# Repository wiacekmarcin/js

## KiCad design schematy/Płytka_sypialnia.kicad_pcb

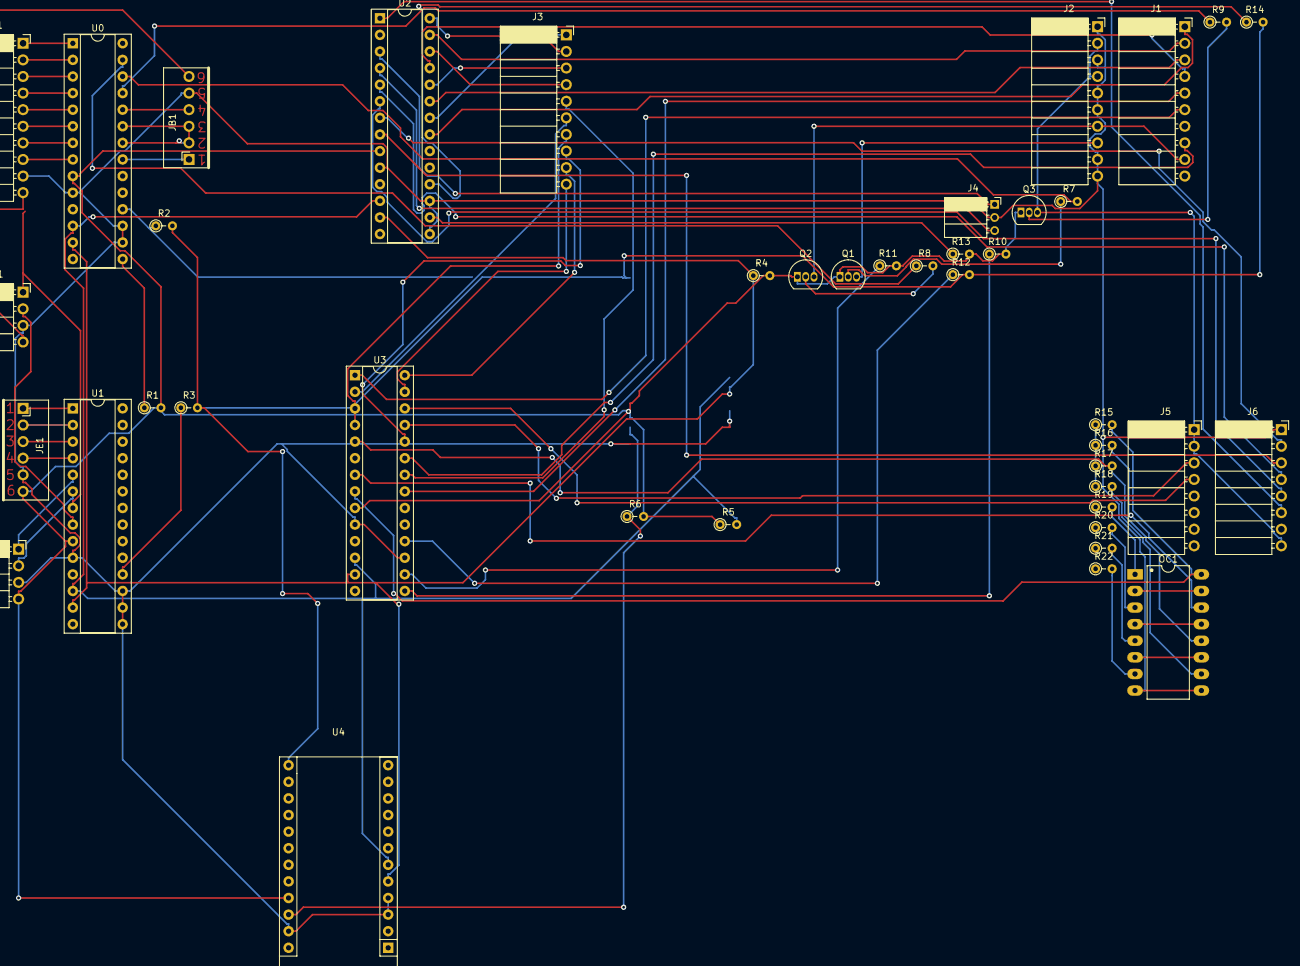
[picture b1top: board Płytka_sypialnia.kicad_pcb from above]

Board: 2 copper layers, 42 parts (0 on the bottom side), 80 nets.

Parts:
J1: F214; PinSocket_1x10_P2.54mm_Horizontal
J2: G215; PinSocket_1x10_P2.54mm_Horizontal
J3: H216; PinSocket_1x10_P2.54mm_Horizontal
J4: I217; PinSocket_1x03_P2.00mm_Horizontal
J5: K59; PinSocket_1x08_P2.54mm_Horizontal
J6: J58; PinSocket_1x08_P2.54mm_Horizontal
JA1: A209; PinSocket_1x10_P2.54mm_Horizontal
JB1: B213; PinSocket_Yellow_1x06_P2.54mm_Horizontal
JC1: C211; PinSocket_1x04_P2.54mm_Horizontal
JD1: D212; PinSocket_1x04_P2.54mm_Horizontal
JE1: E210; PinSocket_Yellow_1x06_P2.54mm_Horizontal
OC1: ILQ621-X006; DIP-16_W10.16mm_LongPads
Q1, Q2, Q3: BC337; TO-92_Inline
R1, R2, R3, R6, R10, R11, R12, R13, R14: 10K; R_Axial_DIN0204_L3.6mm_D1.6mm_P2.54mm_Vertical
R4, R5: 4.7K; R_Axial_DIN0204_L3.6mm_D1.6mm_P2.54mm_Vertical
R7, R8, R9: 100; R_Axial_DIN0204_L3.6mm_D1.6mm_P2.54mm_Vertical
R15, R16, R17, R18: 4.7k; R_Axial_DIN0204_L3.6mm_D1.6mm_P2.54mm_Vertical
R19, R20, R21, R22: 470; R_Axial_DIN0204_L3.6mm_D1.6mm_P2.54mm_Vertical
U0, U1, U2, U3: MCP23017_SP; DIP-28_W7.62mm_Socket
U4: Sparkfun_Pro_Micro

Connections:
2TARYFA: OC1.10, R18.2
5V_CONST: JD1.4, JE1.6, Q1.1 (C), Q2.1 (C), Q3.1 (C), R1.2, R4.2, R5.1, R6.2, R10.2, R11.2, R13.2, U0.9 (VDD), U1.9 (VDD), U2.9 (VDD), U3.9 (VDD), U4.21 (VCC)
5V_OFF: JA1.10, JB1.6, JC1.4
/MCP0_B0: JE1.1, U1.1 (GPB0)
/MCP0_B1: JE1.2, U1.2 (GPB1)
/MCP0_B2: JE1.3, U1.3 (GPB2)
/MCP0_B3: JE1.4, U1.4 (GPB3)
/MCP0_B4: JD1.1, U1.5 (GPB4)
/MCP0_B5: JD1.2, U1.6 (GPB5)
/MCP0_B6: JC1.1, U1.7 (GPB6)
/MCP0_B7: JC1.2, U1.8 (GPB7)
/MCP1_A0: JB1.1, U0.21 (GPA0)
/MCP1_A1: JB1.2, U0.22 (GPA1)
/MCP1_A2: JB1.3, U0.23 (GPA2)
/MCP1_A3: JB1.4, U0.24 (GPA3)
/MCP1_A4: R9.1, U0.25 (GPA4)
/MCP1_A5: R7.2, U0.26 (GPA5)
/MCP1_A6: R8.1, U0.27 (GPA6)
/MCP1_B0: JA1.1, U0.1 (GPB0)
/MCP1_B1: JA1.2, U0.2 (GPB1)
/MCP1_B2: JA1.3, U0.3 (GPB2)
/MCP1_B3: JA1.4, U0.4 (GPB3)
/MCP1_B4: JA1.5, U0.5 (GPB4)
/MCP1_B5: JA1.6, U0.6 (GPB5)
/MCP1_B6: JA1.7, U0.7 (GPB6)
/MCP1_B7: JA1.8, U0.8 (GPB7)
/PODSW_HOL: J1.9, J2.7, Q2.3 (E)
/PODSW_MIX: J2.8, Q1.3 (E)
/PODSW_SAL: J2.2, J2.4, J5.1, J5.2, J6.8, Q3.3 (E)
GND: J2.1, J2.3, J2.5, J2.6, J2.9, J2.10, J4.2, J6.1, JA1.9, JB1.5, JC1.3, JD1.3, JE1.5, OC1.2, OC1.4, OC1.6, OC1.8, OC1.9, OC1.11, OC1.13, OC1.15, U0.10 (VSS), U0.16 (A1), U0.17 (A2), U1.10 (VSS), U1.15 (A0), U1.16 (A1), U1.17 (A2), U2.10 (VSS), U2.15 (A0), U2.17 (A2), U3.10 (VSS), U3.17 (A2), U4.3 (GND), U4.4 (GND), U4.23 (GND)
I2C_SCK: R5.2, U0.12 (SCK), U1.12 (SCK), U2.12 (SCK), U3.12 (SCK), U4.6 (~D3)
I2C_SDA: R4.1, U0.13 (SDA), U1.13 (SDA), U2.13 (SDA), U3.13 (SDA), U4.5 (D2)
KL_HOL_DRZWI: J3.10, U3.27 (GPA6)
KL_HOL_L_L: J1.8, U3.23 (GPA2)
KL_HOL_L_P: J3.8, U3.24 (GPA3)
KL_HOL_P_1: J3.9, U3.28 (GPA7)
KL_HOL_SL_P: J3.7, U3.3 (GPB2), U3.4 (GPB3)
KL_HOL_SP_L: J1.6, U3.1 (GPB0)
KL_HOL_SP_P: J3.6, U3.2 (GPB1)
KL_HOL_W_L: J5.3, U3.25 (GPA4)
KL_HOL_W_P: J5.4, U3.26 (GPA5)
KL_SAL_JL_L: J6.2, U2.7 (GPB6)
KL_SAL_JL_P: J6.3, U2.8 (GPB7)
KL_SAL_JP_L: J6.4, U2.5 (GPB4)
KL_SAL_JP_P: J6.5, U2.6 (GPB5)
KL_SAL_KL_L: J4.1, U2.3 (GPB2)
KL_SAL_KL_P: J4.3, U2.4 (GPB3)
KL_SAL_KP_L: J6.6, U2.1 (GPB0)
KL_SAL_KP_P: J6.7, U2.2 (GPB1)
KL_SAL_L: J1.2, U2.27 (GPA6)
KL_SAL_L_L: J1.5, U3.21 (GPA0)
KL_SAL_L_P: J3.5, U3.22 (GPA1)
KL_SAL_P: J3.2, U2.28 (GPA7)
KL_SAL_SL_L: J1.3, U2.23 (GPA2)
KL_SAL_SL_P: J3.3, U2.24 (GPA3)
KL_SAL_SP_L: J1.4, U2.25 (GPA4)
KL_SAL_SP_P: J3.4, U2.26 (GPA5)
KL_SYP_L: J1.1, U2.21 (GPA0)
KL_SYP_P: J3.1, U2.22 (GPA1)
NOC: OC1.14, R16.2, U3.7 (GPB6)
unnamed: OC1.1, R19.2
unnamed: OC1.3, R20.2
unnamed: OC1.5, R21.2
unnamed: OC1.7, R22.2
unnamed: Q1.2 (B), R7.1
unnamed: Q2.2 (B), R8.2
unnamed: Q3.2 (B), R9.2
unnamed: R15.1, R16.1, R17.1, R18.1
unnamed: R1.1, U0.15 (A0)
unnamed: R2.1, U0.18 (~RESET)
unnamed: R3.1, U1.18 (~RESET)
unnamed: R13.1, U2.16 (A1)
unnamed: R14.1, U2.18 (~RESET)
unnamed: R10.1, U3.15 (A0)
unnamed: R11.1, U3.16 (A1)
unnamed: R12.1, U3.18 (~RESET)
unnamed: R6.1, U4.22 (RST)
RESET_MCP: R2.2, R3.2, R12.2, R14.2, U4.13 (~D10/A10)
WIECZOR: OC1.16, R15.2, U3.8 (GPB7)
ZAS.AWAR: OC1.12, R17.2, U3.5 (GPB4)

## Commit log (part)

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2024-01-02 Kolejna wersja
2024-01-03 Porzadki z mysensor - kompilacja
2024-02-07 Przeniesiono bazę na rapsberry plus dodanie 204-207 przewody
2025-01-23 Wersja przed scalaniem
2025-01-24 Jakies zmiany
2025-01-24 Pierwsza wersja
2025-01-24 Drobne porawki
2025-01-24 szczegoly przeniesione do przewody.details
2025-01-24 Dodano elementy płytkowe i piny do elementów płytkowych
2025-01-24 Zmiana tabeli miejsca
2025-01-24 Dodano urżądzenia końcowe
2025-01-24 Uporządkowano listę miejsc
2025-01-24 Zmiana koncepcji listy przewodow
2025-01-24 Jakieś zmiany
2025-01-24 Poprawki dotyczace przewodu_list
2025-01-24 Drobne poprawki
2025-01-24 Działająca wersja przewodów
2025-01-24 Przed wprowaddzeniem ng-include
2025-01-24 Dodano obsługę połączeń
2025-01-24 Dodano pliki od dodawania polaczenia, zlacza, zyly
2025-01-24 Dodawanie nazwanych łącz cz I (nieskoczone)
2025-01-24 Połączenie na płytce widok
2025-01-24 Dodawanie zakończeń po stronie płutki zakończone
2025-01-24 Dodawanie żył i połączeń
2025-01-24 Rozpoczęcie zmian z dodawaniem połączeń na płytkach
2025-01-24 dodano zlacze_add
2025-01-24 Uzupelniono liste miejsc
2025-01-24 Dodano obsluge edycji i dodawania nowego złącza
2025-01-24 Dodano "dodawanie zakonczenia"
2025-01-24 Ostatnie zmiany przed rewolucja (zlacze_id i miejsce_id w jednje tabeli jako podwójny index zamiast jednego)
2025-01-24 Drobne poprawki z wyświetlaniem
2025-01-24 Zrobione kolory miejsca
2025-01-24 Dodawanie.zakonczenia part 2/3
2025-01-24 Przewody wystwielanie edycja dodawanie
2025-01-24 Dodano elementy plytki
2025-01-24 Spacje
2025-01-24 Zmiana z tinyint na smallint dla elementy_plytkowe
2025-01-24 Drobne poprawki w wyglądzie przewodów
2025-01-24 Poprawki w bazie
2025-01-24 Zmiany w przewodach
2025-01-24 Kolejne praca nad przewodami
2025-01-24 Uporządkowano przewody - przed zmiany w tablicy polaczenia
2025-01-24 Poprawiono elementy płytkowe
2025-01-24 Dodano dodawanie żył
2025-01-24 Dodano zakonczenia
2025-01-24 Wersja z dodawanie pinow do zakonczenia
2025-01-24 Troche danych
2025-01-24 Sporo nowych danych
2025-01-24 Dodano urządzenia kablowe
2025-01-24 Przed wkopiowaniem nowych polaczen
2025-01-24 Wstawianie pinow do urzadzen kablowych - nie testowane
2025-01-24 Dodano definicje plytki A
2025-01-24 Dodano wstawianie żył
2025-01-24 Rozpoczeęcie prac nad dodawanie pinów do złacza
2025-01-24 Dodano wejsje min plikow angular i angular-route
2025-01-24 Porządki w rozdzielni
2025-01-24 Dodano polaczneia plytki B w przedpokoju
2025-01-24 Dodano przeplywomierz dla lazienki
2025-01-24 Kolejne żyły
2025-01-24 Doanie przewodu 29 ze złaczami i wtyczkami
2025-01-24 Zmiany związane dodaniem złacza-właczki.
2025-01-24 Dalsze prace nad przepływomierzami
2025-01-24 zmiany w sql
2025-01-24 Dodawanie w bazie danych
2025-01-24 Poprawki i nowae dane
2025-01-24 Przeniesiono do katalogu przewody
2025-01-24 Wersja 25-01-24
2025-01-24 Dodanie PrzeplywomierzaDomowego
2025-01-24 Zmiana katalogu
2025-01-24 Initial version
2025-01-24 Pierwsze testy nie udane
2025-01-24 Porzadki z katalogiem
2025-01-24 [WC] Poprawka z temperaturą
2025-01-24 Dodanie settings.json
2025-01-24 WC przesunięcie do katalogu
2025-01-24 jakas wersja
2025-01-24 Poprawki w extensions.json
2025-01-24 initial
2025-01-24 Ddaonie funkcji print dla wyjsc
2025-01-24 Porządki
2025-01-24 Pierwsza kompilujaca sie wersja
2025-01-24 Uporzadkowano lustro
2025-01-24 Wersja do testowania
2025-01-24 Testy i testy Prosta wersja
2025-01-24 testy z wersja testowa
2025-01-24 Werjsa z debug
2025-01-24 Pierwsza wgrywana wersja
2025-01-24 przebudowa
2025-01-24 Dziala przycik - nacisniecie klawisza 1 raz, dwa, trzy, przytrzymanie
2025-01-24 Dodano opis algorytmu
2025-01-24 Polaczenie klasy lustra z lampa - jako wynik swiatlo
2025-01-24 Wersja 1
2025-01-24 Zmiany
2025-01-24 Poprawki po rebase
2025-01-24 Poprawki przy initial commit
2025-01-24 Poprawki z ip
2025-01-24 zmiany pod biblioteke
2025-01-24 pogoda
2025-01-24 biblioteka qjson
2025-01-24 Poprawki
2025-01-24 Czcionki i obrazki
2025-01-24 Kolejne poprawki
2025-01-24 Dodano zegarek i ikony od wschod/zachod
2025-01-24 Dodatki xml
2025-01-24 prace nad rs
2025-01-24 Dalsze prace nad pogodą
2025-01-24 Dodanie funkcji dla beafort
2025-01-24 Poprawki na raspberry
2025-01-24 dodano komende system
2025-01-24 konwersja do 4.8
2025-01-24 Na sztywno rss
2025-01-24 Dodanie temperatury
2025-01-24 Usunieicie plikow
2025-01-24 Drobne zmiany
2025-01-24 Bez plikow
2025-01-24 Poprawiono json dla qt4
2025-01-24 Przygotowanie pod pogode za 5 dni
2025-01-24 Kolejby etap
2025-01-24 zmiany fonta
2025-01-24 Przejscie na puqt
2025-01-24 Poprawiono qrcode
2025-01-24 Dodano qrcode
2025-01-24 Poprawka ekranu
2025-01-24 poprawki w wyswietlaniu
2025-01-24 Debug-zamiany
2025-01-24 Poprawki z czcionka
2025-01-24 printscreany
2025-01-24 zmiany pod 6.4
2025-01-24 Dodano biliboteke qrencode
2025-01-24 Progrnoza na 2 dni
2025-01-24 Kolejne zmiany w python
2025-01-24 Usunieto nie potrzebne pliki
2025-01-24 Dodano kolejny dzien
2025-01-24 Dodano śnieg i descz
2025-01-24 Dodano pogoda5
2025-01-24 Usuniete nieptorzebne pliki z iliba
2025-01-24 Poprawk ko
2025-01-24 Kolejna wwersja
2025-01-24 Ostatnie zmiany przed przerobka
2025-01-24 bramkaMqtt
2025-01-24 Initial init
2025-01-24 Dojscie do ladu z wejsciam - cos nie tak z jadalnia down
2025-01-24 Uporzadkowano klasy
2025-01-24 Działająca wersja bez rotacji.
2025-01-24 Wersja z dzialająca rotacja
2025-01-24 Wersja do testowania. Bez algorytmu zgaszania swiatla.
2025-01-24 Poprawki do rotacji
2025-01-24 Wersja z poprawiono rotacja
2025-01-24 Dodano funkcje sprawdzajace nacisniecie klawiszy
2025-01-24 Przetestowana wersja. Nie ma tylko reakcji na czujniki ruchu.
2025-01-24 Przetestowano wlaczniki noc/wieczor/dzien
2025-01-24 Dostosowanie swiatla jadalni do lampy (mozliwosc zapalania od 1 do 7)
2025-01-24 Dzialajaca wersja kuchni z nowa plytka
2025-01-24 Dodano inicjalizacje obiektu wejsciowego
2025-01-24 Nowa plytka
2025-01-24 Zmiany dotyczące dodanie sygnału Zas. awaryjne
2025-01-24 Poprawki dotyczace nowej plytki
2025-01-24 porzadek z katalogiem
2025-01-24 Nie wiem co to
2025-01-24 Poprawka daty
2025-01-24 porzadki
2025-01-24 Porzadki 2
2025-01-24 Dodanie widgetu lazienka
2025-01-24 Dodano poczatki widgetu pogody
2025-01-24 Dodano odczytywanie rss
2025-01-24 Wykomentowano listowanie czcionek
2025-01-24 Dodano statystyki
2025-01-24 Dzisiejsze zmiany
2025-01-24 Poprawki z widget lazienka
2025-01-24 Zegar, zegar analogowy, pogoda
2025-01-24 KOlejne prace nad pogoda widget
2025-01-24 Dodano pogoda widgetu pododa5_1day do pogody
2025-01-24 Dodano parsowanie 5day
2025-01-24 Wersja z generowanym dlugiem i pogoda dla 5 dni
2025-01-24 Drobne zmiany w wygladzie
2025-01-24 Pliki z kredytami
2025-01-24 Poprawki kredytowe
2025-01-24 Poprawki z kredytami
2025-01-24 Jakis merg
2025-01-24 Porpawki z kredytami
2025-01-24 Porzadkowanie kredytow
2025-01-24 Zapomniane zmiany
2025-01-24 Poprawiono tworzenie kredytow
2025-01-24 Poprawki z wyświetlaniem temperatury w łazience
2025-01-24 Poprawiono wersje kredytow
2025-01-24 zmiany w json
2025-01-24 Porzadki po rebase
2025-01-24 Initali commit pio
2025-01-24 Ddodano nowe funkcjonalności
2025-01-24 Pierwsza działająca wersja światła
2025-01-24 pierwsza dzialajaca wersja
2025-01-24 Porzadek z katalogami
2025-01-24 Porzadki z katalogami
2025-01-24 plik zlacza_list2.php
2025-03-05 rozpiska pinow dla plytki sypialnia
2025-03-08 Poprawki przy aplikacji fullscrean
2025-03-09 Algorytm wlaczania swiatla salon/sypialnia. Hol do uzupełnienia
2025-03-10 Podzial na pliki
2025-03-22 Dodano algorytm wlaczania swiatla dla sypialnia/hol/salon
2025-03-22 Weresja kontrolera Sypialnia przed testowaniem
2025-03-24 Kolejne prace nad python/c++
2025-03-27 Poprawki bledow
2025-08-02 Uporządkowanie zmian
2025-08-07 Program do testowania kontrolera
2025-08-13 Zmiany w kontrolerze.
2025-08-13 Zmiany w porotokole
2025-10-12 Ostatnie zmiany w bazie danych
2025-10-12 Dodano katalog je i plik nazy danch a także skrypt ha_ina219.py
2025-10-12 Dodano stronę www
2025-10-13 Czysktki w kodzie przeplywomierza
2025-10-13 Czystki w kodzie przeplywomierza
2025-10-14 Pozbycie się klasy MySensors
2025-10-16 Finalna wersja przepływomierza i skryptu do MQTT_Discovery
2025-10-19 Poprawki przy aplikacji GUI salon
2025-10-27 Poprawka plytki A rozdzielnia glowna
2025-11-18 Dodanie funkcjonalności od ogrzewania
2025-11-22 Jakies skrypty HA
2025-12-03 Dodanie addona do HA
2025-12-22 Addon Energy - dodano wirtualne urzadzenia
2025-12-22 Dodano wirtualne urzadzenia
2025-12-22 Zmiana słowa Test
2025-12-29 wersja 1.2
2025-12-29 addon wersja 2.0
2025-12-29 Wersja dodatku 2.0.1
2025-12-29 Wersja 2.1.0 dodatku
2026-01-02 zmiany przy wykresie
2026-01-04 Zmiany w fullscrean
2026-02-07 Zachowanie zmian dla sterj wersji
2026-03-09 Zmiany w programie dla WC plus symulator
